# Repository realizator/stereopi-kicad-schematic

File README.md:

# StereoPi

This repo contains StereoPi schematics in KiCad. 
Originally, all schematics have been created in Altium, and now we're in the process of porting them to KiCad.

### Project site: 

http://stereopi.com

### Project Wiki:

https://wiki.stereopi.com

### Project forum:

https://forum.stereopi.com

**Special thanks to Twitter user @Knochi**

This man has achieved the gargantuan feat of drawing the first edition of our KiCad schematic from scratch!

Yes, this project is **Open Source**, and has been succesfully crowdfunded here:
https://www.crowdsupply.com/virt2real/stereopi

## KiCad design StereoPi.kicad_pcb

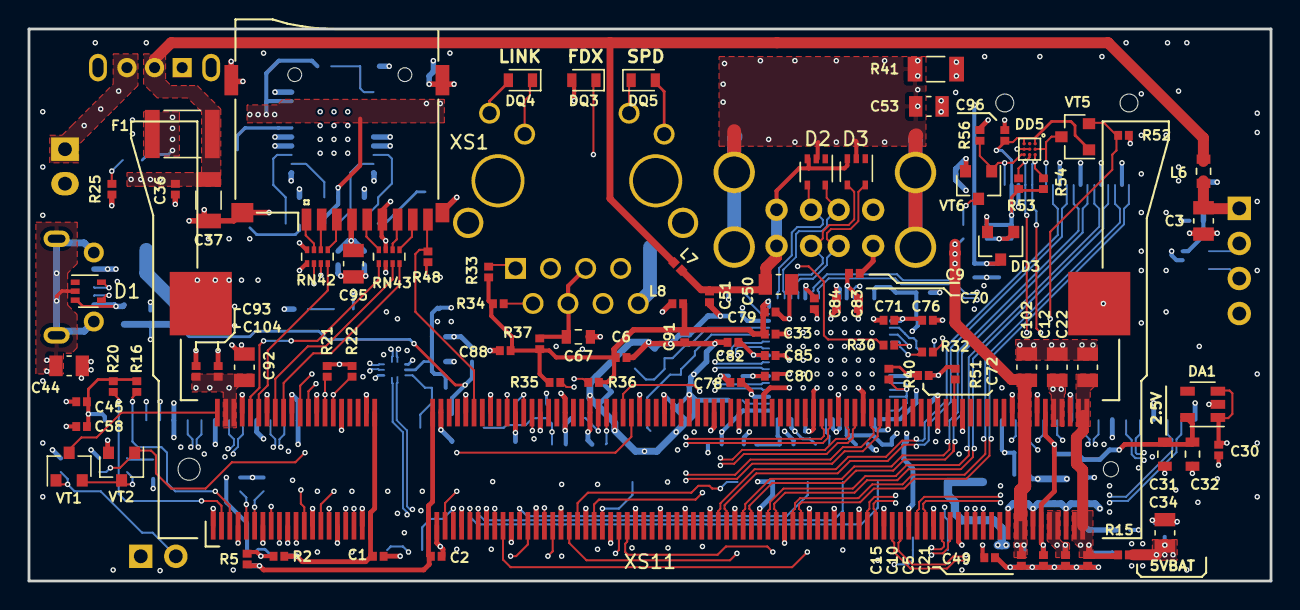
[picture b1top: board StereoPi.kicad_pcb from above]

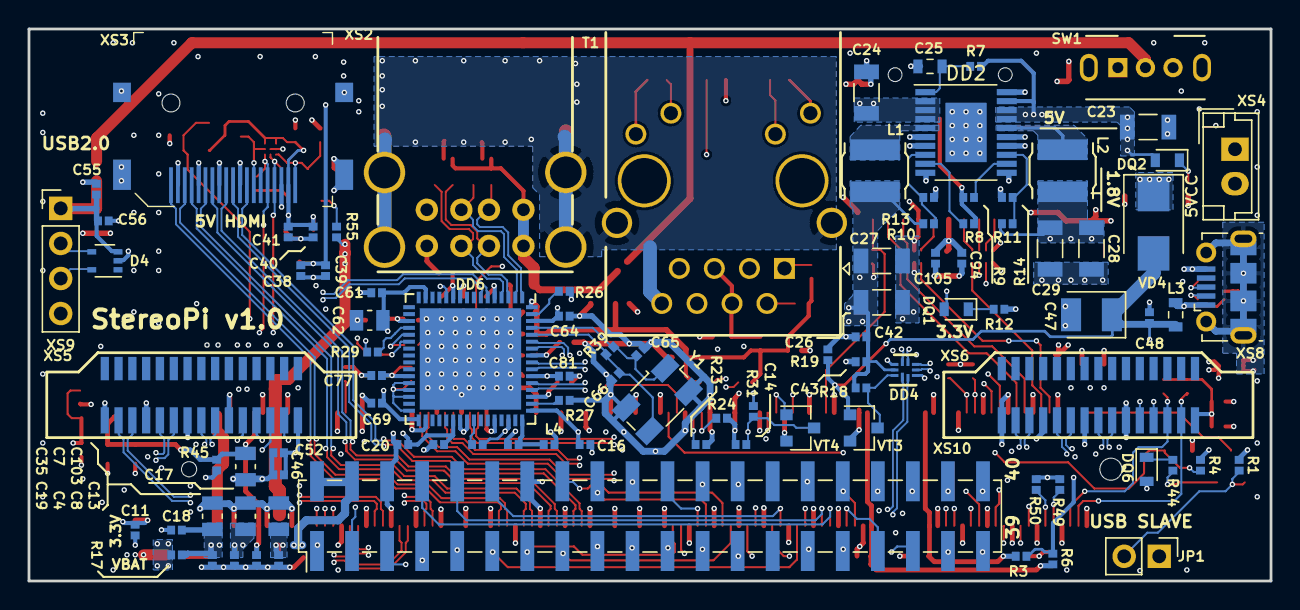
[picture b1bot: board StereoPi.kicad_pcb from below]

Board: 6 copper layers, 90.0 x 40.0 mm, 187 parts (98 on the bottom side), 141 nets.

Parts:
C1, C2, C20, C30, C64: 1u; C_0402_1005Metric
C3, C7, C12, C17, C22, C34, C35, C50, C102, C103: 10u; C_0805_2012Metric
C4, C8, C9, C13, C18, C19, C33, C38, C41, C42, C52, C56, C58, C61, C76, C77, C80, C85, C104, C105: 10n; C_0402_1005Metric
C5, C6, C10, C11, C14, C15, C16, C21, C36, C39, C40, C43, C45, C46, C48, C49, C51, C55, C60, C63, C69, C70, C71, C72, C78, C79, C81, C82, C83, C84, C88, C91, C93, C94, C96: 100n; C_0402_1005Metric
C23, C24, C26, C27, C28, C29, C37: 22u; C_1206_3216Metric
C25, C32: 470n; C_0603_1608Metric
C31: 2u2; C_0603_1608Metric
C44, C53: 1nF; C_0805_2012Metric
C47: 10u/10V; CP_EIA-3528-15_AVX-H
C62, C92, C95: 4u7; C_0805_2012Metric
C65, C66: 33p; C_0402_1005Metric
C67: 22n; C_0603_1608Metric
D1, D2, D3, D4: SP3003-02; SOT-353_SC-70-5
DA1: TPS70625; SOT-23-5
DD2: LM26420; HTSSOP-20-1EP_4.4x6.5mm_P0.65mm_ThermalPad_Ti
DD3: AP2331SA-7; SOT-23
DD4: FSUBS42UMX; UMLP-10_1.4x1.8x0.5mm_P0.4mm
DD5: ESD5384; WLCSP-9_1.14x1.14mm_P0.4mm
DD6: LAN9513; QFN-64-1EP_9x9mm_P0.5mm
DQ1, DQ2, DQ3, DQ4, DQ5, DQ6: KP-1608SCG; LED_0603_1608Metric
F1: MF-MSMF200-2; Fuse_1812_4532Metric
JP1: Conn_01x02; PinHeader_1x02_P2.54mm_Vertical
L1, L2: 1uH 4A; L_Bourns-SRN4018
L3, L6: 2A, 120r; L_0603_1608Metric
L4, L7, L8: 1.3A 120r; L_0402_1005Metric
R1, R8, R9, R18, R55, R56: 47k; R_0402_1005Metric
R2, R3, R5, R6, R15, R17, R45: 0r; R_0402_1005Metric
R4, R23, R24: 100k; R_0402_1005Metric
R7: 5r1; R_0402_1005Metric
R10: 31k6; R_0402_1005Metric
R11: 12k7; R_0402_1005Metric
R12, R25, R29, R30, R32, R44: 470r; R_0402_1005Metric
R13, R14: 10k; R_0402_1005Metric
R16, R19, R20, R21, R22, R28, R31, R40, R48, R49, R50, R51, R52, R53, R54: 4k7; R_0402_1005Metric
R26: 12k; R_0402_1005Metric
R27: 12k4; R_0402_1005Metric
R33, R34, R35, R36: 49r9; R_0402_1005Metric
R37: 10r; R_0402_1005Metric
R39: 1M; R_0402_1005Metric
R41: 1M; R_1206_3216Metric
RN42, RN43: 22; R_Array_Concave_4x0402
SW1: SW_SPDT; SK12D07VG3
T1: Pulse_J0011D01BNL; Conn_RJ45_Transformer_LEDs
VD4: SSB44; D_SMB
VT1, VT2, VT3, VT5, VT6: IRML2502TR; SOT-23
VT4: PDTC143ET; SOT-23
XS1: Micro_SD_Card_Det; Conn_uSDcard
XS2: USB_A_double; CON_USB-A_2-port
XS3: HDMI_A; HDMI_A_Female_2000-1-2-41-00-BK
XS4: EH 2pol; JST_EH_B02B-EH-A_1x02_P2.50mm_Vertical
XS5, XS6: FPC 15pol; FPC-15_VERTICAL_2
XS8: USB_B_Micro; USB_Micro-B_Molex-105017-0001
XS9: Conn_01x04; PinHeader_1x04_P2.54mm_Vertical
XS10: Raspberry_Pi_2_3; PinHeader_2x20_P2.54mm_Vertical_SMD
XS11: S0DIMM DDR2 Standard; Conn_TE-DDR2-SODIMM-0.6-200P-doublesided
Y1: 25MHz; Crystal_SMD_Abracon_ABM3B-4Pin_5.0x3.2mm

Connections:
1V8: C13.1, C15.1, C28.1, C29.1, C102.1, C103.1, L2.2, R3.2, R4.1, R6.2, R11.1, R55.1, XS11.183, XS11.184, XS11.185, XS11.186
3V3: C4.1, C5.1, C7.1, C9.1, C12.1, C26.1, C27.1, C30.1, C42.1, C43.1, C45.2, C46.2, C49.1, C52.2, C58.2, C69.1, C70.1, C71.1, C72.1, C76.1, C77.1, C92.1, C93.1, C94.1, C95.1, C104.1, C105.1, DA1.1, DA1.3, DD4.9, DD6.11, DD6.19, DD6.27, DD6.33, DD6.39, DD6.40, DD6.46, DQ1.2, DQ3.2, DQ4.2, DQ5.2, DQ6.2, L1.1, L8.1, R2.2, R5.2, R10.2, R16.1, R17.2, R18.1, R20.1, R21.1, R22.1, R28.1, R31.1, R40.1, R45.2, R48.2, R49.1, R50.1, R52.1, T1.9, T1.12, XS1.4, XS5.15, XS6.15, XS10.1, XS10.17, XS11.4, XS11.6, XS11.191, XS11.192, XS11.193, XS11.194
5VCC: C11.1, C23.1, C24.1, C34.1, C38.1, C39.1, DD2.2, DD2.3, DD2.4, DD2.17, DD2.18, DD2.19, DD3.3, DQ2.2, F1.1, R7.2, R8.2, R9.2, R15.2, XS10.2, XS10.4
5VCC_EXT: C36.1, C37.1, F1.2, L6.1, L7.1, SW1.2, VD4.1
5VCC_HDMI: C40.1, C41.1, C96.2, DD3.2, DD5.A1, DD5.C1, R53.1, R54.1, VT5.1, XS3.18
5V_EXT: SW1.3, XS4.1
+1V8_CORE: C20.1, C60.1, C61.1, C62.1, DD6.15, DD6.38
+1V8_ETH: C63.1, DD6.48, L4.2
+3V3A: C6.1, C16.1, C33.1, C78.1, C79.1, C80.1, C81.1, C82.1, C83.1, C84.1, C85.1, C88.1, C91.1, DD6.5, DD6.10, DD6.49, DD6.51, DD6.54, DD6.57, DD6.64, L8.2, R33.1, R34.1, R35.1, R36.1, R37.1
+5V_USB_BOOT: C47.1, C48.1, JP1.1, L3.1, R19.2, VD4.2, VT3.1
/Main/CAM0_IO0: R24.1, XS6.11, XS11.82
/Main/CAM0_IO1: XS6.12, XS11.66
/Main/CAM0_SCL: R16.2, XS6.13, XS11.5
/Main/CAM0_SDA: R20.2, XS6.14, XS11.3
/Main/CAM1_IO0: R23.1, XS5.11, XS11.84
/Main/CAM1_IO1: XS5.12, XS11.60
/Main/CAM1_SCL: R22.2, XS5.13, XS11.30
/Main/CAM1_SDA: R21.2, XS5.14, XS11.28
/Main/GPIO14_TXD0: XS10.8, XS11.51
/Main/GPIO15_RXD0: XS10.10, XS11.53
/Main/GPIO16: XS10.36, XS11.57
/Main/GPIO17: XS10.11, XS11.59
/Main/GPIO18_PWM0: XS10.12, XS11.63
/Main/GPIO19_MISO1: XS10.35, XS11.65
/Main/GPIO20_MOSI1: XS10.38, XS11.69
/Main/GPIO21_SLCK1: XS10.40, XS11.71
/Main/GPIO22: XS10.15, XS11.75
/Main/GPIO23: XS10.16, XS11.77
/Main/GPIO24: XS10.18, XS11.81
/Main/GPIO25: XS10.22, XS11.83
/Main/GPIO26: XS10.37, XS11.87
/Main/GPIO27: XS10.13, XS11.89
/Main/HDMI_CLK_N: XS3.12, XS11.111
/Main/HDMI_CLK_P: XS3.10, XS11.113
/Main/HDMI_D0_N: XS3.9, XS11.117
/Main/HDMI_D0_P: XS3.7, XS11.119
/Main/HDMI_D1_N: XS3.6, XS11.123
/Main/HDMI_D1_P: XS3.4, XS11.125
/Main/HDMI_D2_N: XS3.3, XS11.129
/Main/HDMI_D2_P: XS3.1, XS11.131
/Main/HDMI_SCL: DD5.A3, R54.2, XS3.15, XS11.175
/Main/HDMI_SDA: DD5.B3, R53.2, XS3.16, XS11.173
/Main/SD_CLK: RN43.1, XS11.10
/Main/SD_CMD: RN42.4, XS11.12
/Main/SD_DAT0: RN43.3, XS11.16
/Main/SD_DAT1: RN43.4, XS11.18
/Main/SD_DAT2: RN42.2, XS11.22
/Main/SD_DAT3: RN42.3, XS11.24
/Main/SD_DETECT: R48.1, XS1.9, XS11.52
/Power/1V8_SW: DD2.16, L2.1
/Power/3V3_SW: DD2.5, L1.2
/Power/EMMC_DISABLE_N: VT1.3, XS11.2
/Power/EMMC_EN_N_1V8: R4.2, VT2.1, XS11.90
/USB LAN/5V_USB0_EXT: C50.1, C51.1, D2.3, D3.3, L7.2, XS2.1, XS2.5
/USB LAN/5V_USB2_EXT: C3.1, C55.1, C56.1, D4.3, L6.2, XS9.1
/USB LAN/5V_USB_BOOT_EXT: D1.3, L3.2, XS8.1
/USB LAN/ETH_RX_N: DD6.53, R36.2, T1.6
/USB LAN/ETH_RX_P: DD6.52, R35.2, T1.3
/USB LAN/ETH_TX_N: DD6.56, R34.2, T1.2
/USB LAN/ETH_TX_P: DD6.55, R33.2, T1.1
/USB LAN/HARD_RESET: C14.1, DD6.12, R31.2, VT4.3
/USB LAN/USB2_N: D2.4, DD6.1, XS2.2
/USB LAN/USB2_P: D2.5, DD6.2, XS2.3
/USB LAN/USB3_N: D3.4, DD6.3, XS2.6
/USB LAN/USB3_P: D3.5, DD6.4, XS2.7
/USB LAN/USB4_N: D4.4, DD6.6, XS9.2
/USB LAN/USB4_P: D4.5, DD6.7, XS9.3
/USB LAN/USB_HSD2_N: DD4.6, DD6.58
/USB LAN/USB_HSD2_P: DD4.7, DD6.59
/USB LAN/USB_HSD_N: D1.4, DD4.4, XS8.2
/USB LAN/USB_HSD_P: D1.5, DD4.5, XS8.3
/USB LAN/VDD18USBPLL: C64.1, DD6.62, L4.1
/USB LAN/nFDX: DD6.20, R29.2
/USB LAN/nFDX_LED: DQ3.1, R29.1
/USB LAN/nLINKA: DD6.21, R30.2
/USB LAN/nLINKA_LED: DQ4.1, R30.1, T1.10
/USB LAN/nSPD: DD6.22, R32.2
/USB LAN/nSPD_LED: DQ5.1, R32.1, T1.11
DAC_2V5: C8.1, C10.1, C17.1, C31.1, C32.1, DA1.5, R45.1, XS11.189, XS11.190
GND: C1.2, C2.2, C3.2, C4.2, C5.2, C6.2, C7.2, C8.2, C9.2, C10.2, C11.2, C12.2, C13.2, C14.2, C15.2, C16.2, C17.2, C18.2, C19.2, C20.2, C21.2, C22.2, C23.2, C24.2, C25.2, C26.2, C27.2, C28.2, C29.2, C30.2, C31.2, C32.2, C33.2, C34.2, C35.2, C36.2, C37.2, C38.2, C39.2, C40.2, C41.2, C42.2, C43.2, C44.2, C45.1, C46.1, C47.2, C48.2, C49.2, C50.2, C51.2, C52.1, C53.2, C55.2, C56.2, C58.1, C60.2, C61.2, C62.2, C63.2, C64.2, C65.2, C66.2, C67.2, C69.2, C70.2, C71.2, C72.2, C76.2, C77.2, C78.2, C79.2, C80.2, C81.2, C82.2, C83.2, C84.2, C85.2, C88.2, C91.2, C92.2, C93.2, C94.2, C95.2, C96.1, C102.2, C103.2, C104.2, C105.2, D4.2, DA1.2, DD2.6, DD2.7, DD2.10, DD2.11, DD2.14, DD2.15, DD2.20, DD2.21, DD3.1, DD4.3, DD4.8, DD5.B2, DD5.C2, DD6.34, DD6.44, DD6.65, R1.2, R12.1, R13.2, R14.2, R19.1, R23.2, R24.2, R25.1, R26.2, R27.2, R41.2, R51.1, R56.2, RN42.1, RN42.8, RN43.2, RN43.7, VT2.2, VT3.2, VT4.2, VT6.2, XS1.6, XS1.10, XS2.4, XS2.8, XS3.2, XS3.5, XS3.8, XS3.11, XS3.17, XS3.SH, XS4.2, XS5.1, XS5.4, XS5.7, XS5.10, XS6.1, XS6.4, XS6.7, XS6.10, XS8.5, XS9.4, XS10.6, XS10.9, XS10.14, XS10.20, XS10.25, XS10.30, XS10.34, XS10.39, XS11.1, XS11.7, XS11.8, XS11.13, XS11.14, XS11.19, XS11.20, XS11.25, XS11.26, XS11.31, XS11.32, XS11.37, XS11.38, XS11.43, XS11.44, XS11.49, XS11.50, XS11.55, XS11.56, XS11.61, XS11.62, XS11.67, XS11.68, XS11.73, XS11.74, XS11.79, XS11.80, XS11.85, XS11.86, XS11.91, XS11.92, XS11.97, XS11.98, XS11.103, XS11.104, XS11.109, XS11.110, XS11.115, XS11.116, XS11.121, XS11.122, XS11.127, XS11.133, XS11.134, XS11.139, XS11.140, XS11.145, XS11.146, XS11.151, XS11.152, XS11.157, XS11.163, XS11.164, XS11.169, XS11.170, XS11.181, XS11.182, XS11.187, XS11.188, XS11.195, XS11.196, Y1.2, Y1.4
GPIO38_RESET: VT4.1, XS11.64
unnamed: C1.1, R2.1, R3.1, XS11.39, XS11.40
unnamed: C2.1, R5.1, R6.1, XS11.41, XS11.42
unnamed: C25.1, DD2.1, R7.1
unnamed: C65.1, DD6.61, R39.1, Y1.1
unnamed: C66.1, DD6.60, R39.2, Y1.3
unnamed: C67.1, R37.2, T1.4, T1.5
unnamed: DD2.8, R10.1, R13.1
unnamed: DD2.9, R8.1
unnamed: DD2.12, R9.1
unnamed: DD2.13, R11.2, R14.1
unnamed: DD4.1, XS11.165
unnamed: DD4.2, XS11.167
unnamed: DD4.10, R18.2, VT3.3
unnamed: DD5.A2, VT5.3, XS3.13
unnamed: DD5.C3, R56.1, VT6.1, XS3.19
unnamed: DD6.28, DD6.29, DD6.30, DD6.32, R40.2
unnamed: DD6.41, R28.2
unnamed: DD6.50, R27.1
unnamed: DD6.63, R26.1
unnamed: DQ1.1, R12.2
unnamed: DQ2.1, R25.2
unnamed: DQ6.1, R44.1
unnamed: JP1.2, R1.1, VT1.1
unnamed: R44.2, VT1.2, VT2.3
unnamed: R49.2, XS10.3, XS11.9
unnamed: R50.2, XS10.5, XS11.11
unnamed: R51.2, XS11.168
unnamed: R52.2, VT5.2, XS11.171
unnamed: R55.2, VT6.3, XS11.88
unnamed: RN42.5, XS1.3
unnamed: RN42.6, XS1.2
unnamed: RN42.7, XS1.1
unnamed: RN43.5, XS1.8
unnamed: RN43.6, XS1.7
unnamed: RN43.8, XS1.5
unnamed: XS10.7, XS11.15
unnamed: XS10.19, XS11.33
unnamed: XS10.21, XS11.29
unnamed: XS10.23, XS11.35
unnamed: XS10.24, XS11.27
unnamed: XS10.26, XS11.23
unnamed: XS10.29, XS11.17
unnamed: XS10.31, XS11.21
unnamed: XS10.32, XS11.45
unnamed: XS10.33, XS11.47
unnamed: XS6.3, XS11.136
unnamed: XS6.2, XS11.138
unnamed: XS6.9, XS11.142
unnamed: XS6.8, XS11.144
unnamed: XS5.9, XS11.147
unnamed: XS6.6, XS11.148
unnamed: XS5.8, XS11.149
unnamed: XS6.5, XS11.150
unnamed: XS5.6, XS11.153
unnamed: XS5.5, XS11.155
unnamed: XS5.3, XS11.159
unnamed: XS5.2, XS11.161
SHELF1_GND: C44.1, D1.2, XS8.6
SHELF_GND: C53.1, D2.2, D3.2, R41.1, T1.8, T1.13, XS2.9
VBAT: C18.1, C19.1, C21.1, C22.1, C35.1, R15.1, R17.1, XS11.197, XS11.198, XS11.199, XS11.200

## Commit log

2019-09-10 Readme update
2019-09-10 Layout update
2019-09-10 links update
2019-09-11 2 StereoPi photos added
2019-09-11 Photos added
2019-09-11 layout fix
2019-09-11 typo fixes
2019-09-11 text update
2019-09-12 Apache License
2019-09-18 added Voltages to Caps, reformatted labels
2019-09-18 Innitial commit
2019-09-19 added Voltages to Caps C44 and C53 fixed labels (bold to regular)
2019-09-19 added .gitignore
